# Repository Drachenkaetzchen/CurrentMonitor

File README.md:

WARNING: This project is in transition to become a full-fledged MPPT charge controller for solar projects.
---------

CurrentMonitor is a dual-channel current and voltage monitor based on two INA138 current shunt monitoring ICs and an atmega168 and should run between 3.3 and 5V input (5V tested).

In the given configuration, the maximum values are:

* Input Voltage: 3.3V - 5.5V
* Maximum Monitoring Current: 2A
* Maximum Monitoring Voltage: 25V
* Current Gain: 2 (1mA = 2mV)
* Voltage Dividor: 5 (1M/200k)
* Self Power Usage: 5mA
* Voltage Resolution: 25mV
* Current Resolution: 2mA

The circuit is using the AVR's built-in ADC converter, which has a resolution of 10 bits (1024 values). By adjusting the resistors for the voltage divider and the gain resistor, you can adapt the circuit to your own needs. e.g. if the maximum voltage you want to measure is 10V, you can simply adjust the voltage dividor to 2 and thus have a voltage resolution of about 10mV. The minimum gain for the current is 1; so the minimum resolution one could gain is about 1mA. You could experiment with smaller gain values; the INA138 datasheet doesn't tell what happens then.

No communication or storage is present; you need to add your own I²C and serial communication busses to it.

The schematic uses a mix of through-hole and SMD components, because I wasn't sure if my chosen resitor values would fit; if they wouldn't, I could simply replace them. Feel free to replace them all with SMD resistors. But at the end, it turned out that my calculations were correct; but I haven't gotten around to change all components to SMD.

I'm using a 1% 10k gain resistor, which results in a gain of 2. You can use other values as well; refer to the INA138 datasheet where they listed.

As voltage and current monitoring is pretty much important, I'm planning to sell PCBs with serial, I²C and SD card logging capabilities.

Note that if you change the size of your shunt resistor, you'll also need to re-calculate the power dissipation capabilities. In the current configuration, a 0.5W resistor is suitable for the 2A maximum (voltage drop across the shunt resistor is 0.2 volts, which in turn gives 0.4 watts).

The schematic was done using Eagle 6.4.

The firmware isn't completed and will be uploaded as soon as it's done.

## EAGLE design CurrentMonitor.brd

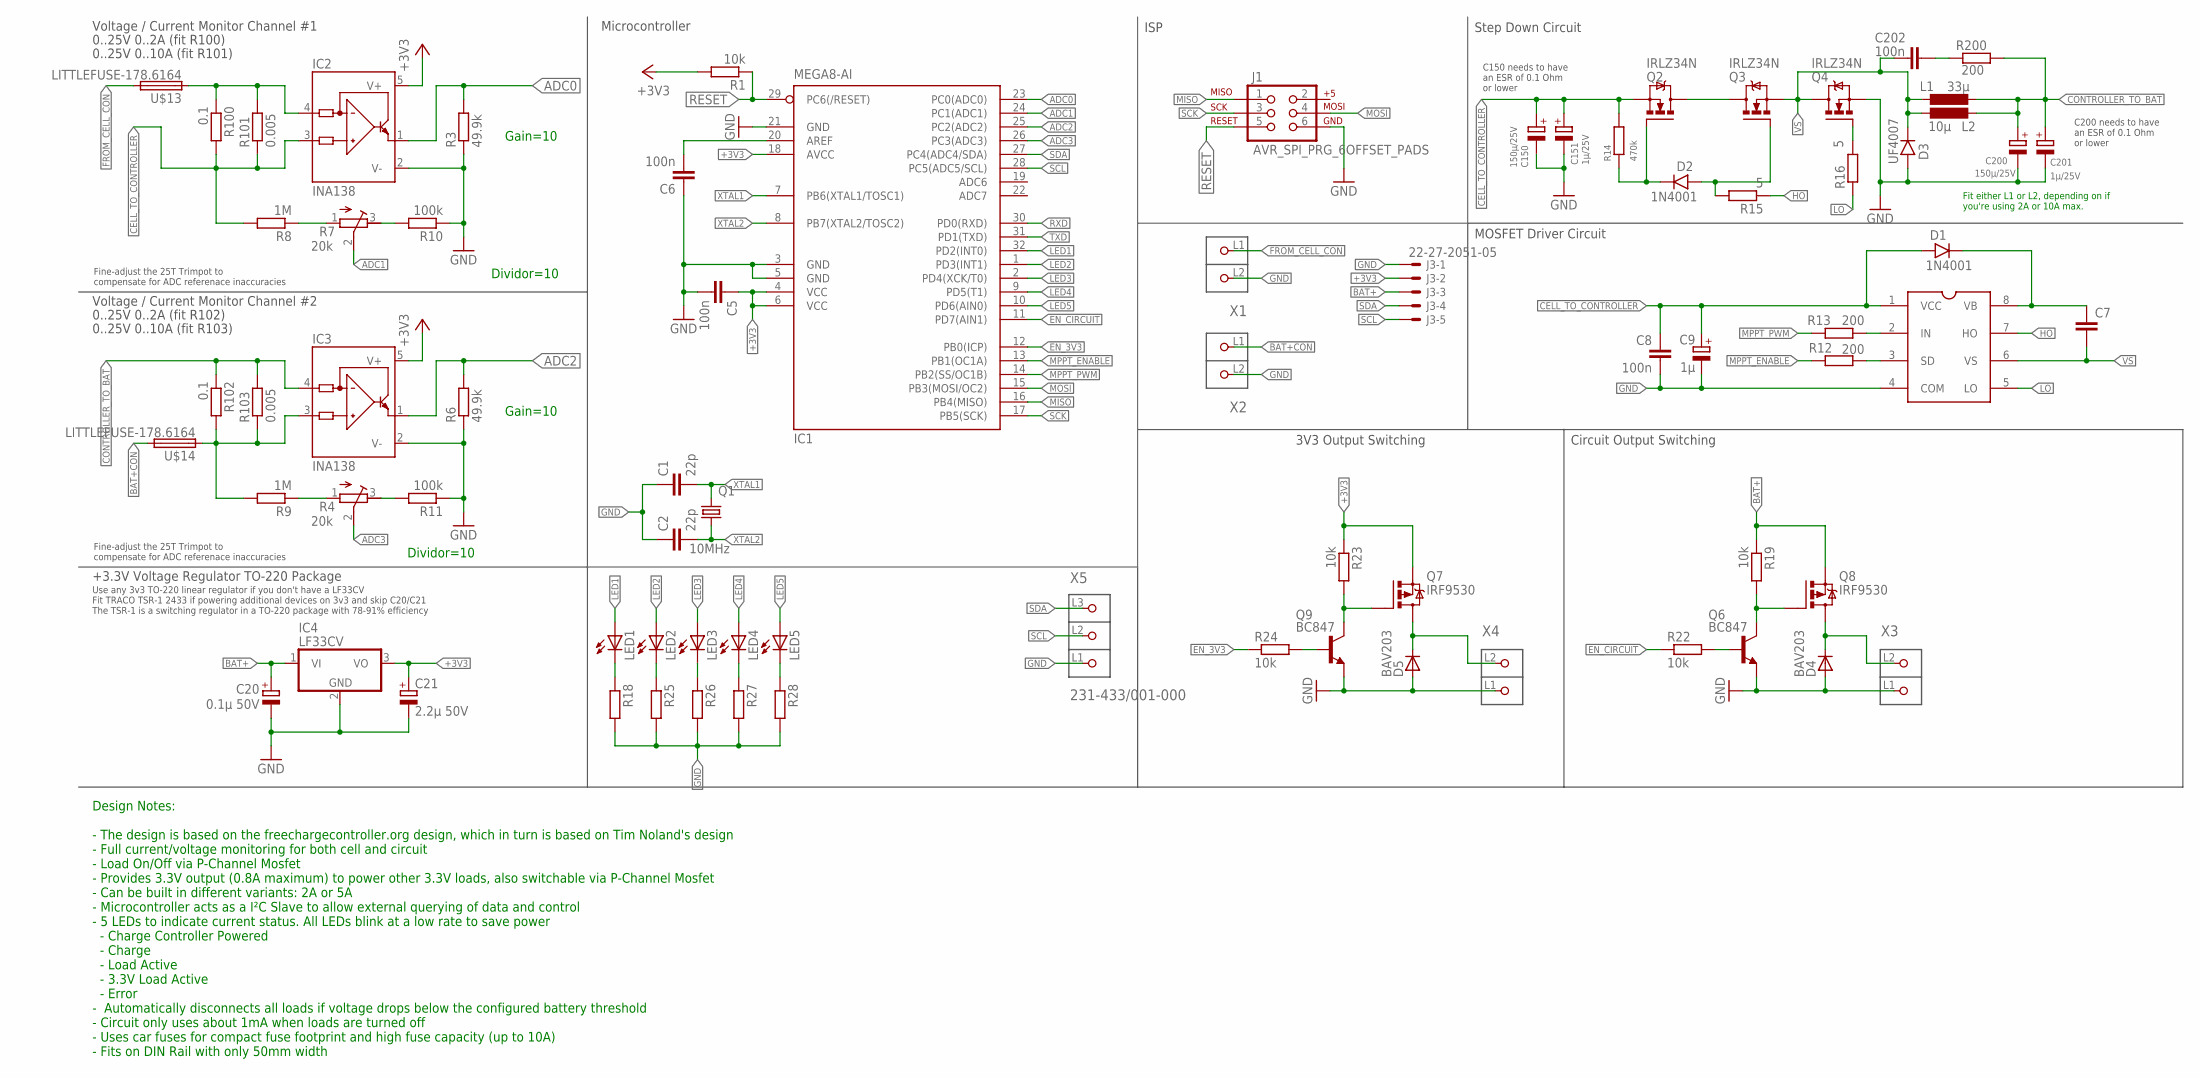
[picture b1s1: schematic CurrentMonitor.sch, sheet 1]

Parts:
C1, C2: 22p; C1206
C5, C6, C8, C202: 100n; C0805
C7: C-EUC0805; C0805
C9: 1µ; PANASONIC_A
C20: 0.1µ 50V; PANASONIC_A
C21: 2.2µ 50V; PANASONIC_B
C150, C200: 150µ/25V; PANASONIC_F
C151, C201: 1µ/25V; PANASONIC_B
D1, D2: 1N4001; DO41-3
D3: UF4007; DO41-3
D4, D5: BAV203; SOD80
IC1: MEGA8-AI; TQFP32-08
IC2, IC3: INA138; SOT23-5
IC4: LF33CV; TO220V
J1: AVR_SPI_PRG_6OFFSET_PADS; 2X3_OFFSET
J3: 22-27-2051-05; 6410-05
L1: 33µ; PISM
L2: 10µ; PISR
LED1, LED2, LED3, LED4, LED5: LEDCHIPLED_1206; CHIPLED_1206
Q1: 10MHz; CTS406
Q2, Q3, Q4: IRLZ34N; TO220BV
Q6, Q9: BC847; SOT23
Q7, Q8: IRF9530; TO220BV
R1, R19, R22, R23, R24: 10k; R0805
R3, R6: 49.9k; R0805
R4, R7: 20k; RTRIM64W
R8, R9: 1M; R0805
R10, R11: 100k; R0805
R12, R13, R200: 200; R0805
R14: 470k; R0805
R15, R16: 5; R0805
R18, R25, R26, R27, R28: R-EU_R0805; R0805
R100, R102: 0.1; R1206
R101, R103: 0.005; R2512
U$1: IR2104S
U$13, U$14: LITTLEFUSE-178.6164; LITTLEFUSE-178-6164
X1, X2, X3, X4: 231-432/001-000; P-231-432/001-000
X5: 231-433/001-000; P-231-433/001-000

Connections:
+3V3: C5.1, C21.+, IC1.4 (VCC), IC1.6 (VCC), IC1.18 (AVCC), IC2.5 (V+), IC3.5 (V+), IC4.3 (VO), J3.2, Q7.S, R1.2, R23.1
ADC0: IC1.23 (PC0(ADC0)), IC2.1 (OUT), R3.2
ADC1: IC1.24 (PC1(ADC1)), R7.2 (S)
ADC2: IC1.25 (PC2(ADC2)), IC3.1 (OUT), R6.2
ADC3: IC1.26 (PC3(ADC3)), R4.2 (S)
BAT+: C20.+, IC3.3 (IN+), IC4.1 (VI), J3.3, Q8.S, R9.2, R19.1, R102.2, R103.1, U$14.P$1 (1)
BAT+CON: U$14.P$2 (2), X2.L1 (P1)
CELL_TO_CONTROLLER: C8.1, C9.+, C150.+, C151.+, D1.A, IC2.3 (IN+), Q2.S, R8.2, R14.2, R100.2, R101.1, U$1.1 (VCC)
CONTROLLER_TO_BAT: C200.+, C201.+, IC3.4 (IN-), L1.2, L2.1, R102.1, R103.2, R200.2
EN_3V3: IC1.12 (PB0(ICP)), R24.1
EN_CIRCUIT: IC1.11 (PD7(AIN1)), R22.1
FROM_CELL: IC2.4 (IN-), R100.1, R101.2, U$13.P$1 (1)
FROM_CELL_CON: U$13.P$2 (2), X1.L1 (P1)
GND: C1.1, C2.1, C5.2, C6.1, C8.2, C9.-, C20.-, C21.-, C150.-, C151.-, C200.-, C201.-, D3.A, D4.2 (A), D5.2 (A), IC1.3 (GND), IC1.5 (GND), IC1.21 (GND), IC2.2 (V-), IC3.2 (V-), IC4.2 (GND), J1.6, J3.1, Q4.S, Q6.2 (E), Q9.2 (E), R3.1, R6.1, R10.1, R11.1, R18.2, R25.2, R26.2, R27.2, R28.2, U$1.4 (COM), X1.L2 (P2), X2.L2 (P2), X3.L1 (P1), X4.L1 (P1), X5.L1 (P1)
HO: R15.1, U$1.7 (HO)
LED1: IC1.32 (PD2(INT0)), LED1.A
LED2: IC1.1 (PD3(INT1)), LED2.A
LED3: IC1.2 (PD4(XCK/T0)), LED3.A
LED4: IC1.9 (PD5(T1)), LED4.A
LED5: IC1.10 (PD6(AIN0)), LED5.A
LO: R16.1, U$1.5 (LO)
MISO: IC1.16 (PB4(MISO)), J1.1
MOSI: IC1.15 (PB3(MOSI/OC2)), J1.4
MPPT_ENABLE: IC1.13 (PB1(OC1A)), R12.1
MPPT_PWM: IC1.14 (PB2(SS/OC1B)), R13.1
unnamed: C6.2, IC1.20 (AREF)
unnamed: R4.3 (E), R11.2
unnamed: R7.3 (E), R10.2
unnamed: R7.1 (A), R8.1
unnamed: R4.1 (A), R9.1
unnamed: LED1.C, R18.1
unnamed: R12.2, U$1.3 (SD)
unnamed: C7.1, D1.C, U$1.8 (VB)
unnamed: R13.2, U$1.2 (IN)
unnamed: Q4.G, R16.2
unnamed: D2.C, Q2.G, R14.1
unnamed: D2.A, Q3.G, R15.2
unnamed: Q2.D, Q3.D
unnamed: D4.1 (C), Q8.D, X3.L2 (P2)
unnamed: C202.1, R200.1
unnamed: LED2.C, R25.1
unnamed: Q6.3 (C), Q8.G, R19.2
unnamed: Q6.1 (B), R22.2
unnamed: Q7.G, Q9.3 (C), R23.2
unnamed: Q9.1 (B), R24.2
unnamed: D5.1 (C), Q7.D, X4.L2 (P2)
unnamed: LED3.C, R26.1
unnamed: LED4.C, R27.1
unnamed: LED5.C, R28.1
RESET: IC1.29 (PC6(/RESET)), J1.5, R1.1
RXD: IC1.30 (PD0(RXD))
SCK: IC1.17 (PB5(SCK)), J1.3
SCL: IC1.28 (PC5(ADC5/SCL)), J3.5, X5.L2 (P2)
SDA: IC1.27 (PC4(ADC4/SDA)), J3.4, X5.L3 (P3)
TXD: IC1.31 (PD1(TXD))
VS: C7.2, C202.2, D3.C, L1.1, L2.2, Q3.S, Q4.D, U$1.6 (VS)
XTAL1: C1.2, IC1.7 (PB6(XTAL1/TOSC1)), Q1.3 (2)
XTAL2: C2.2, IC1.8 (PB7(XTAL2/TOSC2)), Q1.1

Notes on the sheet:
Gain=10
Dividor=10
Voltage / Current Monitor Channel #1
Voltage / Current Monitor Channel #2
0..25V 0..2A (fit R100)
0..25V 0..2A (fit R102)
+3.3V Voltage Regulator TO-220 Package
Use any 3v3 TO-220 linear regulator if you don't have a LF33CV Fit TRACO TSR-1 2433 if powering additional devices on 3v3 and skip C20/C21 The TSR-1 is a switching regulator in a TO-220 package with 78-91% efficiency
Microcontroller
Fine-adjust the 25T Trimpot to compensate for ADC referenace inaccuracies
ISP
Step Down Circuit
MOSFET Driver Circuit
3V3 Output Switching
Circuit Output Switching
Fit either L1 or L2, depending on if you're using 2A or 10A max.
0..25V 0..10A (fit R101)
0..25V 0..10A (fit R103)
C200 needs to have an ESR of 0.1 Ohm or lower
C150 needs to have an ESR of 0.1 Ohm or lower
Design Notes: - The design is based on the freechargecontroller.org design, which in turn is based on Tim Noland's design - Full current/voltage monitoring for both cell and circuit - Load On/Off via P-Channel Mosfet - Provides 3.3V output (0.8A maximum) to power other 3.3V loads, also switchable v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

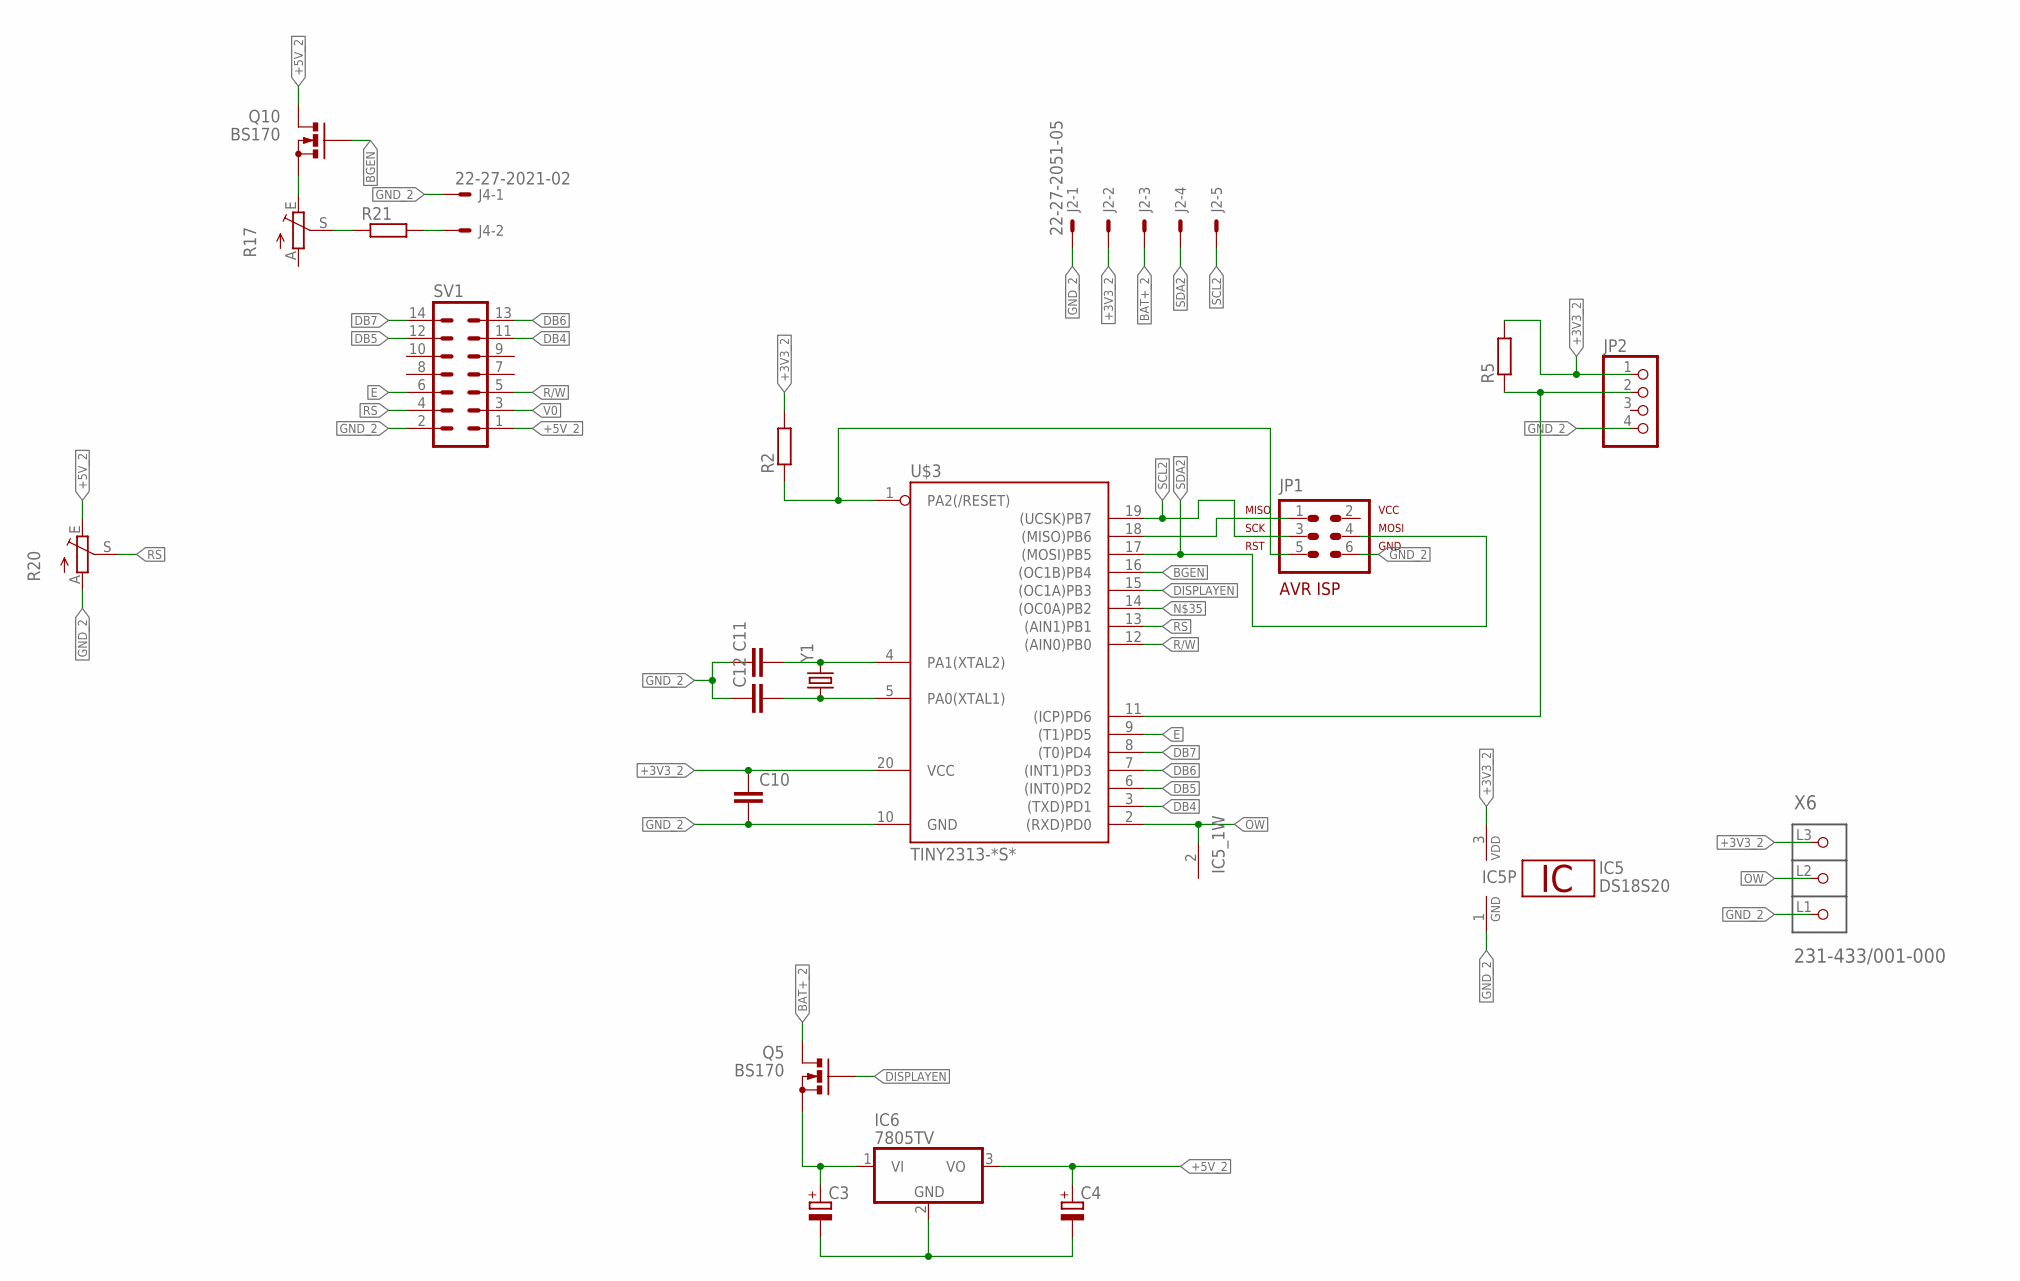
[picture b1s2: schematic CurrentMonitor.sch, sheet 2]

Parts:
C3, C4: CPOL-EUE3.5-8; E3,5-8
C10, C11, C12: C-EUC0805; C0805
IC5: DS18S20; TO92-
IC6: 7805TV; TO220V
J2: 22-27-2051-05; 6410-05
J4: 22-27-2021-02; 6410-02
JP1: AVR-ISP-6VERT; AVR-ISP-6
JP2: PINHD-1X4; 1X04
Q5, Q10: BS170; SOT54E
R2, R5, R21: R-EU_R0805; R0805
R17, R20: TRIM_EU-PT10; PT-10
SV1: ML14
U$3: TINY2313-*S*; SO20L$
X6: 231-433/001-000; P-231-433/001-000
Y1: CRYSTALHC49US; HC49US

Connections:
+3V3_2: C10.1, IC5.3 (VDD), J2.2, JP2.1, R2.2, R5.2, U$3.20 (VCC), X6.L3 (P3)
+5V_2: C4.+, IC6.3 (VO), Q10.D, R20.E, SV1.1
BAT+_2: J2.3, Q5.D
BGEN: Q10.G, U$3.16 ((OC1B)PB4)
DB4: SV1.11, U$3.3 ((TXD)PD1)
DB5: SV1.12, U$3.6 ((INT0)PD2)
DB6: SV1.13, U$3.7 ((INT1)PD3)
DB7: SV1.14, U$3.8 ((T0)PD4)
DISPLAYEN: Q5.G, U$3.15 ((OC1A)PB3)
E: SV1.6, U$3.9 ((T1)PD5)
GND_2: C3.-, C4.-, C10.2, C11.1, C12.1, IC5.1 (GND), IC6.2 (GND), J2.1, J4.1, JP1.6, JP2.4, R20.A, SV1.2, U$3.10 (GND), X6.L1 (P1)
unnamed: JP1.1, U$3.18 ((MISO)PB6)
unnamed: R17.S, R21.1
unnamed: JP2.2, R5.1, U$3.11 ((ICP)PD6)
unnamed: J4.2, R21.2
unnamed: JP1.5, R2.1, U$3.1 (PA2(/RESET))
unnamed: Q10.S, R17.E
unnamed: C11.2, U$3.4 (PA1(XTAL2)), Y1.2
unnamed: C12.2, U$3.5 (PA0(XTAL1)), Y1.1
unnamed: C3.+, IC6.1 (VI), Q5.S
OW: IC5.2 (1W), U$3.2 ((RXD)PD0), X6.L2 (P2)
R/W: SV1.5, U$3.12 ((AIN0)PB0)
RS: R20.S, SV1.4, U$3.13 ((AIN1)PB1)
SCL2: J2.5, JP1.3, U$3.19 ((UCSK)PB7)
SDA2: J2.4, JP1.4, U$3.17 ((MOSI)PB5)
V0: SV1.3

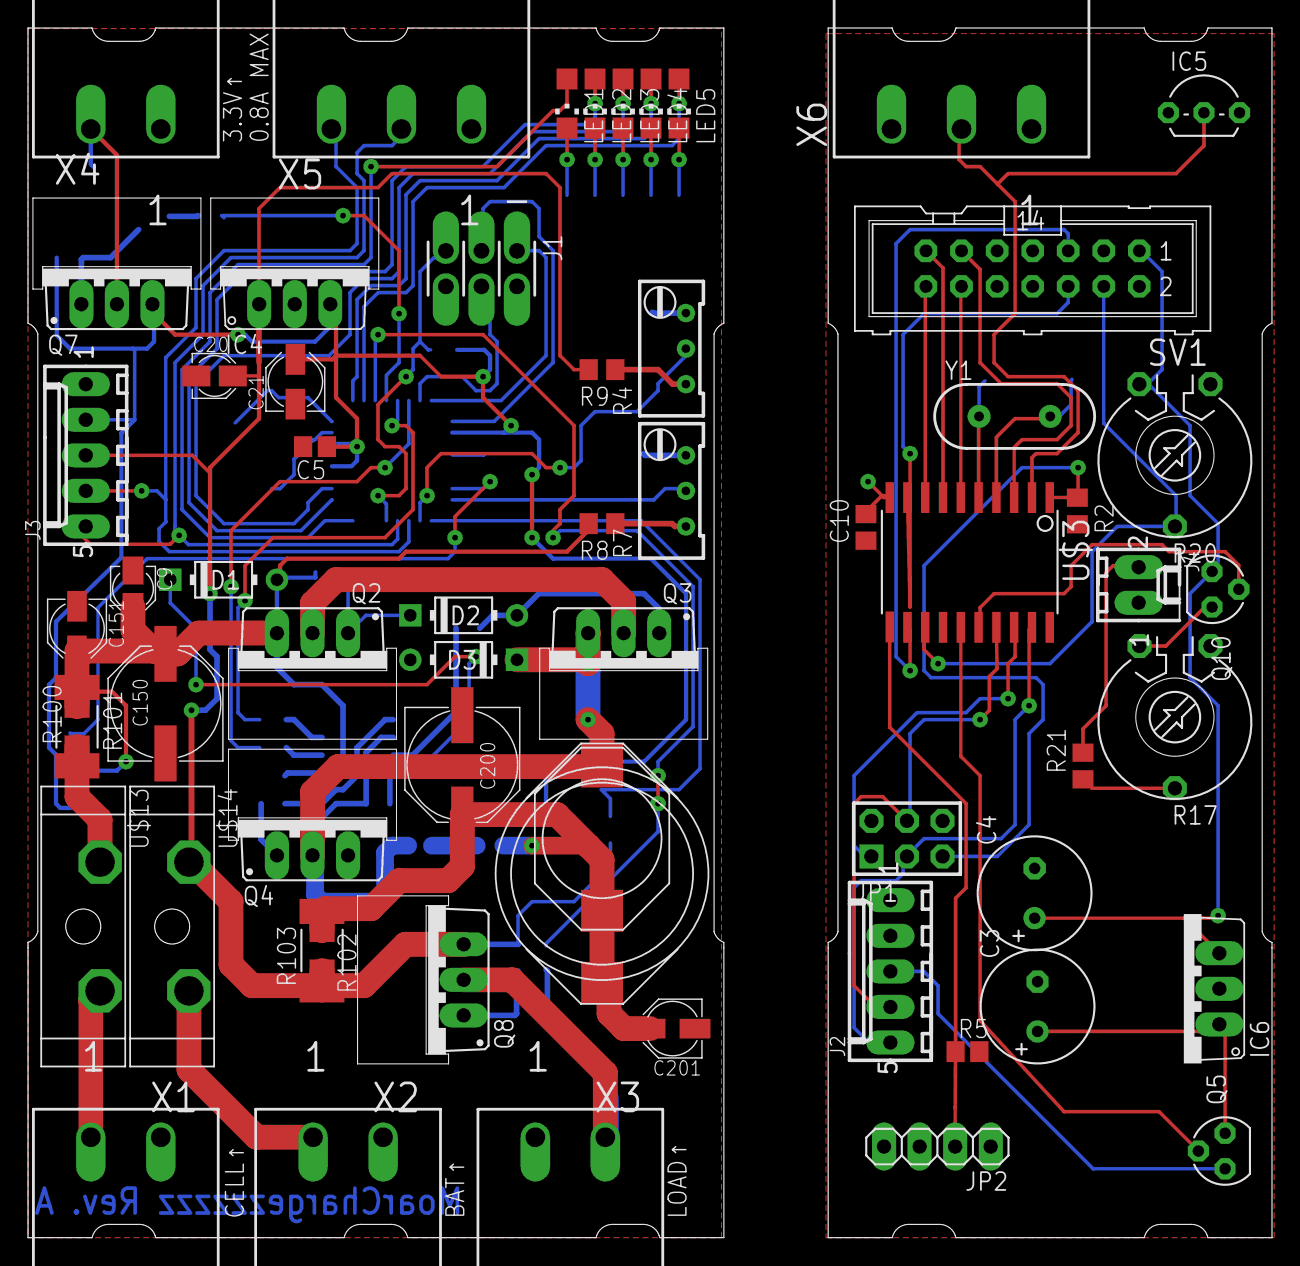
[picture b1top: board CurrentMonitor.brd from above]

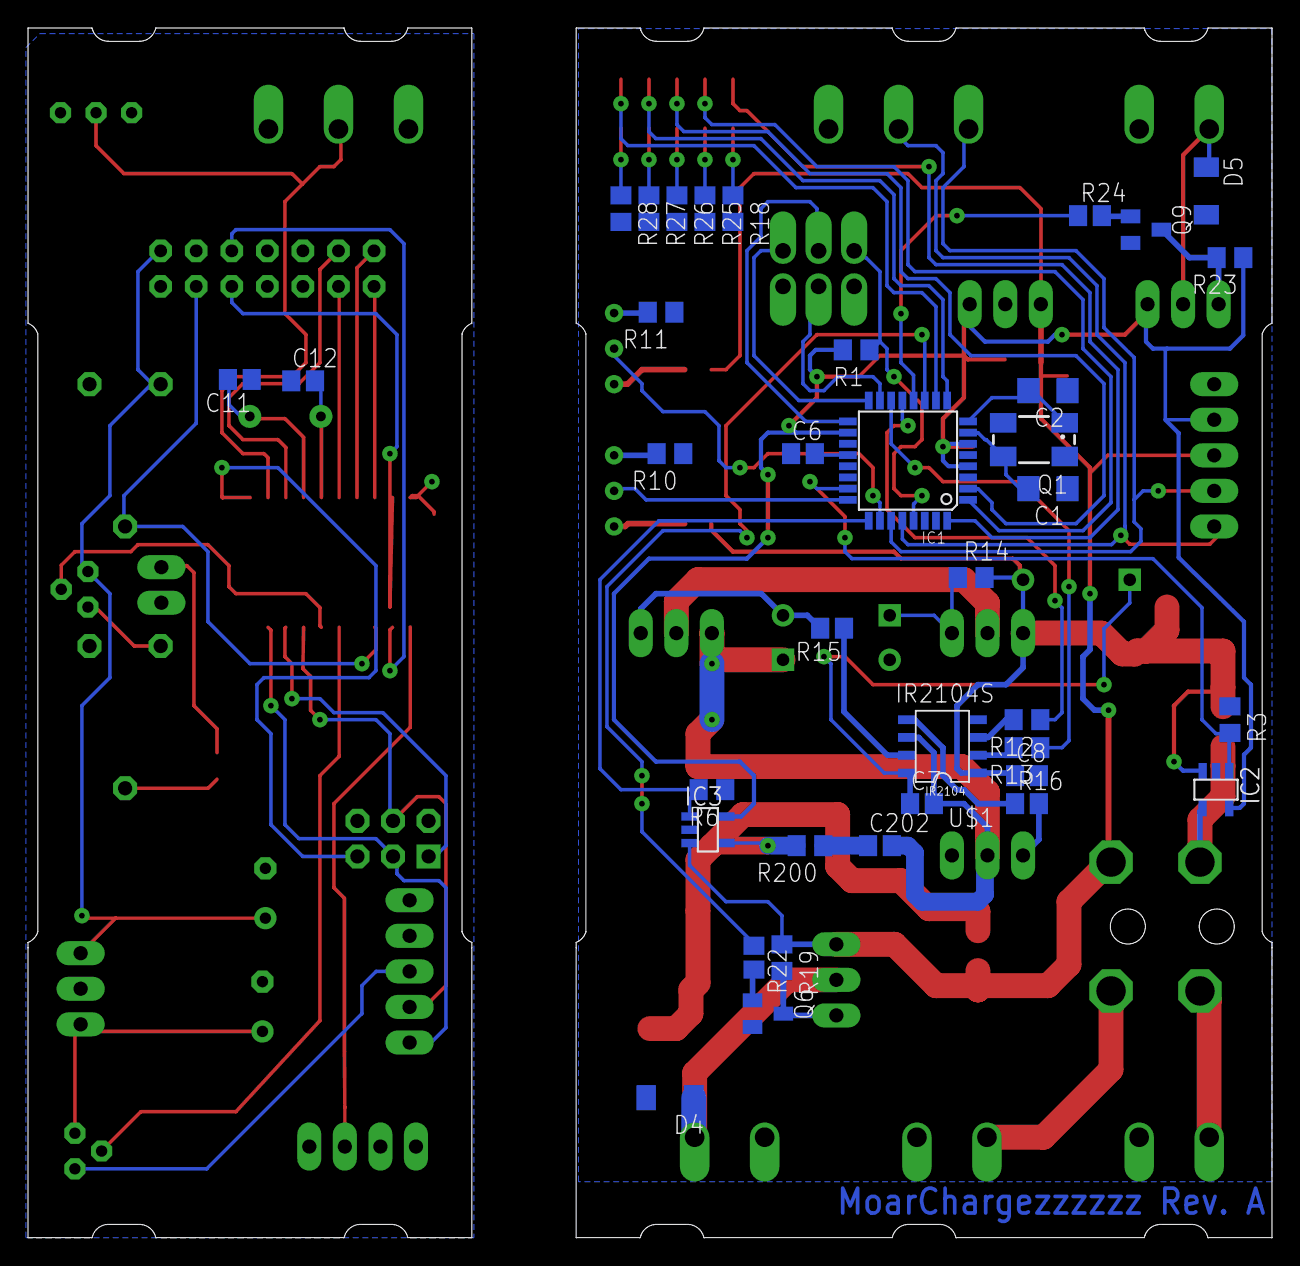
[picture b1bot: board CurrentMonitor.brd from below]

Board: 2 copper layers, 88.9 x 86.4 mm, 106 parts (37 on the bottom side), 81 nets.

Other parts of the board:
U$2: BC35,6
U$6, U$8, U$9, U$10, U$11, U$12: PR5/15-M3
U$7: BC53,6

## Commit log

2013-06-08 Added Firmware
2013-06-14 Redesign first part, more to follow.
2013-06-17 More updates
2013-06-17 Bleh.
2013-06-18 Updated README.md to reflect the transition to a full-fledged charge controller
2013-06-18 Added initial board
2013-06-23 Added initial board. WARNING: This is an ugly board, which didn't receive much love because it's a prototype and I can't etch double-sided boards yet.
2013-06-25 Second revision, dual layer
2013-06-27 Added slightly larger traces and adjusted some components in order to support currents up to 10A
2013-06-27 Added heatsink + LEDs
2013-07-01 Foo (don't know what's changed, but I'm going to reroute everything)
2013-07-18 Few fixes (forgot to commit, forgot what I have changed) ;)

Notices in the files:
parts and their libraries:
SparkFun: Licensing: CC v3.0 Share-Alike You are welcome to use this library for commercial purposes.
